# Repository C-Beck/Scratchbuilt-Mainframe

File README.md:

# Scratchbuilt-Mainframe
Mainframe design based on a z80 microprocessor

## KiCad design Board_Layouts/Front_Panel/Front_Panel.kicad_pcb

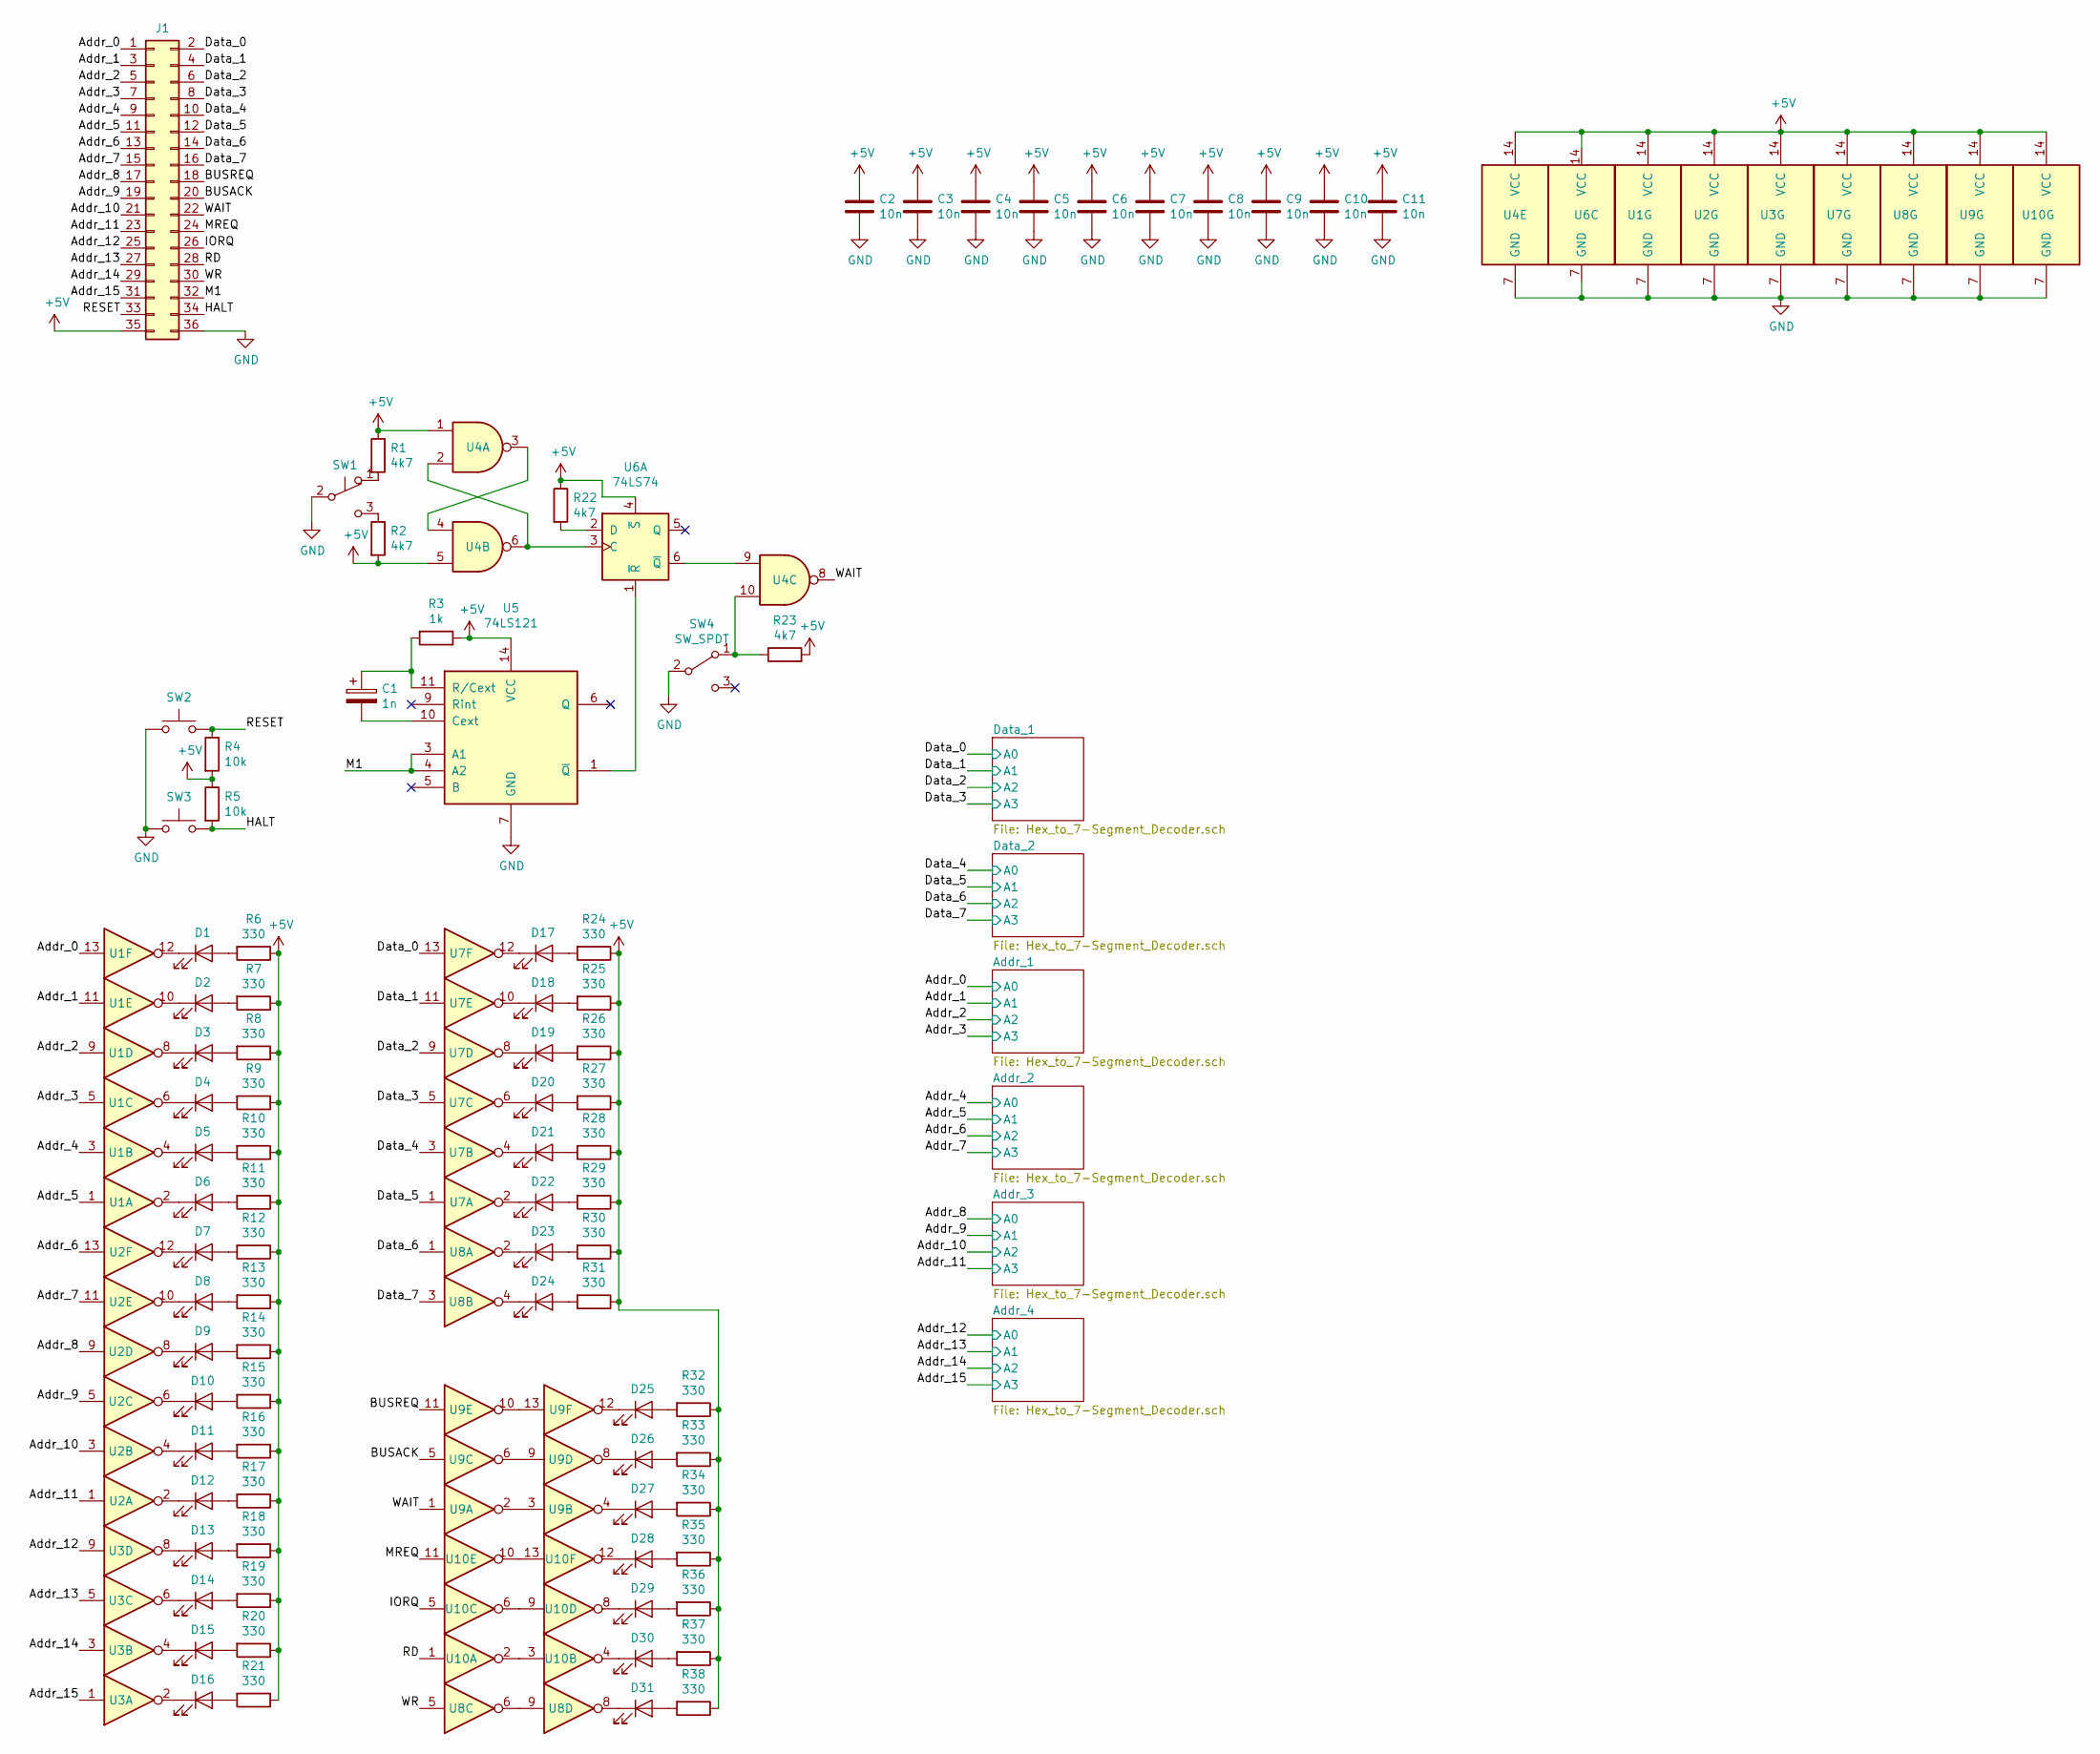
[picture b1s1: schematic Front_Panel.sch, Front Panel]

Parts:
C1: 1n; C_Rect_L4.0mm_W2.5mm_P2.50mm
C2, C3, C4, C5, C6, C7, C8, C9, C10, C11: 10n; C_Rect_L4.0mm_W2.5mm_P2.50mm
D1, D2, D3, D4, D5, D6, D7, D8, D9, D10, D11, D12, D13, D14, D15, D16, D17, D18, D19, D20, D21, D22, D23, D24, D25, D26, D27, D28, D29, D30, D31: LED; LED_D5.0mm
J1: Conn_02x18_Odd_Even; PinHeader_2x18_P2.54mm_Vertical
R1, R2, R22, R23: 4k7; R_Axial_DIN0207_L6.3mm_D2.5mm_P10.16mm_Horizontal
R3: 1k; R_Axial_DIN0207_L6.3mm_D2.5mm_P10.16mm_Horizontal
R4, R5: 10k; R_Axial_DIN0207_L6.3mm_D2.5mm_P10.16mm_Horizontal
R6, R7, R8, R9, R10, R11, R12, R13, R14, R15, R16, R17, R18, R19, R20, R21, R24, R25, R26, R27, R28, R29, R30, R31, R32, R33, R34, R35, R36, R37, R38: 330; R_Axial_DIN0207_L6.3mm_D2.5mm_P10.16mm_Horizontal
SW1: SW_Push_SPDT; PinHeader_1x03_P2.54mm_Vertical
SW2, SW3: SW_Push; PinHeader_1x03_P2.54mm_Vertical
SW4: SW_SPDT; PinHeader_1x03_P2.54mm_Vertical
U1, U2, U3, U7, U8, U9, U10: 74LS04; DIP-14_W7.62mm
U4: 7400; DIP-14_W7.62mm
U5: 74LS121; DIP-14_W7.62mm
U6: 74LS74; DIP-14_W7.62mm

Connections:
+5V: C2.1, C3.1, C4.1, C5.1, C6.1, C7.1, C8.1, C9.1, C10.1, C11.1, J1.35, R1.1, R2.2, R3.1, R4.2, R5.1, R6.1, R7.1, R8.1, R9.1, R10.1, R11.1, R12.1, R13.1, R14.1, R15.1, R16.1, R17.1, R18.1, R19.1, R20.1, R21.1, R22.1, R23.2, R24.1, R25.1, R26.1, R27.1, R28.1, R29.1, R30.1, R31.1, R32.1, R33.1, R34.1, R35.1, R36.1, R37.1, R38.1, U1.14 (VCC), U2.14 (VCC), U3.14 (VCC), U4.1, U4.5, U4.14 (VCC), U5.14 (VCC), U6.4 (~S), U6.14 (VCC), U7.14 (VCC), U8.14 (VCC), U9.14 (VCC), U10.14 (VCC); also elsewhere on the board
/Addr_0: J1.1, U1.13; also elsewhere on the board
/Addr_1: J1.3, U1.11; also elsewhere on the board
/Addr_2: J1.5, U1.9; also elsewhere on the board
/Addr_3: J1.7, U1.5; also elsewhere on the board
/Addr_4: J1.9, U1.3; also elsewhere on the board
/Addr_5: J1.11, U1.1; also elsewhere on the board
/Addr_6: J1.13, U2.13; also elsewhere on the board
/Addr_7: J1.15, U2.11; also elsewhere on the board
/Addr_8: J1.17, U2.9; also elsewhere on the board
/Addr_9: J1.19, U2.5; also elsewhere on the board
/Addr_10: J1.21, U2.3; also elsewhere on the board
/Addr_11: J1.23, U2.1; also elsewhere on the board
/Addr_12: J1.25, U3.9; also elsewhere on the board
/Addr_13: J1.27, U3.5; also elsewhere on the board
/Addr_14: J1.29, U3.3; also elsewhere on the board
/Addr_15: J1.31, U3.1; also elsewhere on the board
/BUSACK: J1.20, U9.5
/BUSREQ: J1.18, U9.11
/Data_0: J1.2, U7.13; also elsewhere on the board
/Data_1: J1.4, U7.11; also elsewhere on the board
/Data_2: J1.6, U7.9; also elsewhere on the board
/Data_3: J1.8, U7.5; also elsewhere on the board
/Data_4: J1.10, U7.3; also elsewhere on the board
/Data_5: J1.12, U7.1; also elsewhere on the board
/Data_6: J1.14, U8.1; also elsewhere on the board
/Data_7: J1.16, U8.3; also elsewhere on the board
/HALT: J1.34, R5.2, SW3.2
/IORQ: J1.26, U10.5
/M1: J1.32, U5.3 (A1), U5.4 (A2)
/MREQ: J1.24, U10.11
/RD: J1.28, U10.1
/RESET: J1.33, R4.1, SW2.2
/WAIT: J1.22, U4.8, U9.1
/WR: J1.30, U8.5
GND: C2.2, C3.2, C4.2, C5.2, C6.2, C7.2, C8.2, C9.2, C10.2, C11.2, J1.36, SW1.2 (B), SW2.1, SW3.1, SW4.2 (B), U1.7 (GND), U2.7 (GND), U3.7 (GND), U4.7 (GND), U5.7 (GND), U6.7 (GND), U7.7 (GND), U8.7 (GND), U9.7 (GND), U10.7 (GND); also elsewhere on the board
unnamed: C1.1, R3.2, U5.11 (R/Cext)
unnamed: C1.2, U5.10 (Cext)
unnamed: D1.1 (K), U1.12
unnamed: D1.2 (A), R6.2
unnamed: D2.1 (K), U1.10
unnamed: D2.2 (A), R7.2
unnamed: D3.1 (K), U1.8
unnamed: D3.2 (A), R8.2
unnamed: D4.1 (K), U1.6
unnamed: D4.2 (A), R9.2
unnamed: D5.1 (K), U1.4
unnamed: D5.2 (A), R10.2
unnamed: D6.1 (K), U1.2
unnamed: D6.2 (A), R11.2
unnamed: D7.1 (K), U2.12
unnamed: D7.2 (A), R12.2
unnamed: D8.1 (K), U2.10
unnamed: D8.2 (A), R13.2
unnamed: D9.1 (K), U2.8
unnamed: D9.2 (A), R14.2
unnamed: D10.1 (K), U2.6
unnamed: D10.2 (A), R15.2
unnamed: D11.1 (K), U2.4
unnamed: D11.2 (A), R16.2
unnamed: D12.1 (K), U2.2
unnamed: D12.2 (A), R17.2
unnamed: D13.1 (K), U3.8
unnamed: D13.2 (A), R18.2
unnamed: D14.1 (K), U3.6
unnamed: D14.2 (A), R19.2
unnamed: D15.1 (K), U3.4
unnamed: D15.2 (A), R20.2
unnamed: D16.1 (K), U3.2
unnamed: D16.2 (A), R21.2
unnamed: D17.1 (K), U7.12
unnamed: D17.2 (A), R24.2
unnamed: D18.1 (K), U7.10
unnamed: D18.2 (A), R25.2
unnamed: D19.1 (K), U7.8
unnamed: D19.2 (A), R26.2
unnamed: D20.1 (K), U7.6
unnamed: D20.2 (A), R27.2
unnamed: D21.1 (K), U7.4
unnamed: D21.2 (A), R28.2
unnamed: D22.1 (K), U7.2
unnamed: D22.2 (A), R29.2
unnamed: D23.1 (K), U8.2
unnamed: D23.2 (A), R30.2
unnamed: D24.1 (K), U8.4
unnamed: D24.2 (A), R31.2
unnamed: D25.1 (K), U9.12
unnamed: D25.2 (A), R32.2
unnamed: D26.1 (K), U9.8
unnamed: D26.2 (A), R33.2
unnamed: D27.1 (K), U9.4
unnamed: D27.2 (A), R34.2
unnamed: D28.1 (K), U10.12
unnamed: D28.2 (A), R35.2
unnamed: D29.1 (K), U10.8
unnamed: D29.2 (A), R36.2
unnamed: D30.1 (K), U10.4
unnamed: D30.2 (A), R37.2
unnamed: D31.1 (K), U8.8
unnamed: D31.2 (A), R38.2
unnamed: R1.2, SW1.1 (A)
unnamed: R2.1, SW1.3 (C)
unnamed: R22.2, U6.2 (D)
unnamed: R23.1, SW4.1 (A), U4.10
unnamed: U4.2, U4.6, U6.3 (C)
unnamed: U4.3, U4.4
unnamed: U4.9, U6.6 (~Q)
unnamed: U5.1 (~Q), U6.1 (~R)
unnamed: U8.6, U8.9
unnamed: U9.2, U9.3
unnamed: U9.6, U9.9
unnamed: U9.10, U9.13
unnamed: U10.2, U10.3
unnamed: U10.6, U10.9
unnamed: U10.10, U10.13

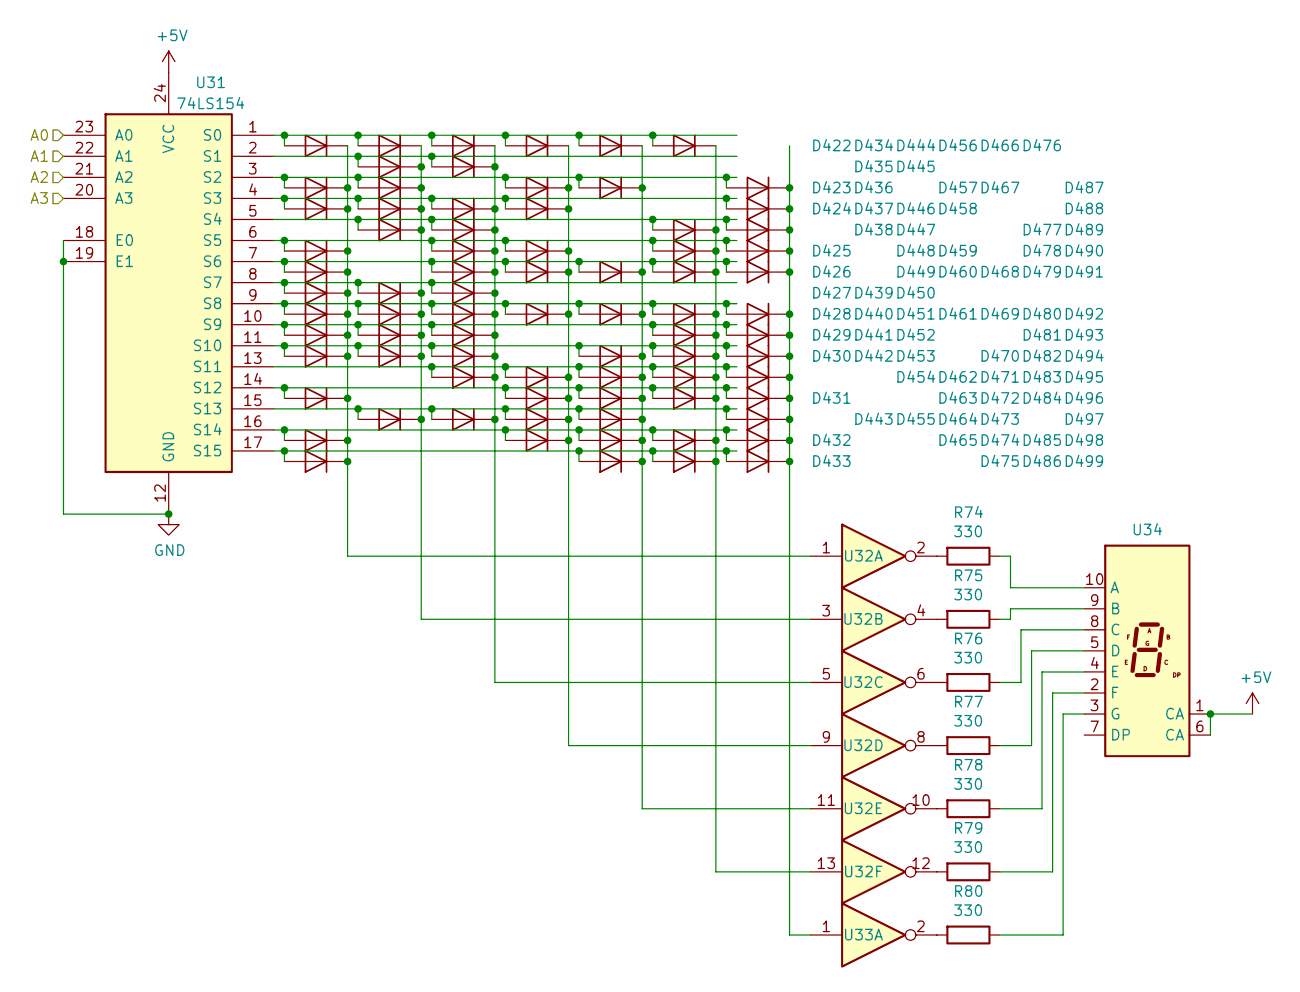
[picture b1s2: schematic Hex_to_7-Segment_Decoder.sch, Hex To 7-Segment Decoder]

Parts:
D32, D33, D34, D35, D36, D37, D38, D39, D40, D41, D42, D43, D44, D45, D46, D47, D48, D49, D50, D51, D52, D53, D54, D55, D56, D57, D58, D59, D60, D61, D62, D63, D64, D65, D66, D67, D68, D69, D70, D71, D72, D73, D74, D75, D76, D77, D78, D79, D80, D81, D82, D83, D84, D85, D86, D87, D88, D89, D90, D91, D92, D93, D94, D95, D96, D97, D98, D99, D100, D101, D102, D103, D104, D105, D106, D107, D108, D109: D; D_SOD-123
R39, R40, R41, R42, R43, R44, R45: 330; R_Axial_DIN0207_L6.3mm_D2.5mm_P10.16mm_Horizontal
U11: 74LS154; DIP-24_W7.62mm
U12, U13: 74LS04; DIP-14_W7.62mm
U14: HDSP-A401

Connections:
+5V: U11.24 (VCC), U14.1 (CA), U14.6 (CA); also elsewhere on the board
/Data_4: U11.23 (A0); also elsewhere on the board
/Data_5: U11.22 (A1); also elsewhere on the board
/Data_6: U11.21 (A2); also elsewhere on the board
/Data_7: U11.20 (A3); also elsewhere on the board
GND: U11.12 (GND), U11.18 (E0), U11.19 (E1); also elsewhere on the board
unnamed: D32.1 (K), D33.1 (K), D34.1 (K), D35.1 (K), D36.1 (K), D37.1 (K), D38.1 (K), D39.1 (K), D40.1 (K), D41.1 (K), D42.1 (K), D43.1 (K), U12.1
unnamed: D32.2 (A), D44.2 (A), D54.2 (A), D66.2 (A), D76.2 (A), D86.2 (A), U11.1 (S0)
unnamed: D33.2 (A), D46.2 (A), D67.2 (A), D77.2 (A), D97.2 (A), U11.3 (S2)
unnamed: D34.2 (A), D47.2 (A), D56.2 (A), D68.2 (A), D98.2 (A), U11.4 (S3)
unnamed: D37.2 (A), D49.2 (A), D60.2 (A), U11.8 (S7)
unnamed: D44.1 (K), D45.1 (K), D46.1 (K), D47.1 (K), D48.1 (K), D49.1 (K), D50.1 (K), D51.1 (K), D52.1 (K), D53.1 (K), U12.3
unnamed: D45.2 (A), D55.2 (A), U11.2 (S1)
unnamed: D48.2 (A), D57.2 (A), D87.2 (A), D99.2 (A), U11.5 (S4)
unnamed: D54.1 (K), D55.1 (K), D56.1 (K), D57.1 (K), D58.1 (K), D59.1 (K), D60.1 (K), D61.1 (K), D62.1 (K), D63.1 (K), D64.1 (K), D65.1 (K), U12.5
unnamed: D66.1 (K), D67.1 (K), D68.1 (K), D69.1 (K), D70.1 (K), D71.1 (K), D72.1 (K), D73.1 (K), D74.1 (K), D75.1 (K), U12.9
unnamed: D76.1 (K), D77.1 (K), D78.1 (K), D79.1 (K), D80.1 (K), D81.1 (K), D82.1 (K), D83.1 (K), D84.1 (K), D85.1 (K), U12.11
unnamed: D86.1 (K), D87.1 (K), D88.1 (K), D89.1 (K), D90.1 (K), D91.1 (K), D92.1 (K), D93.1 (K), D94.1 (K), D95.1 (K), D96.1 (K), U12.13
unnamed: D97.1 (K), D98.1 (K), D99.1 (K), D100.1 (K), D101.1 (K), D102.1 (K), D103.1 (K), D104.1 (K), D105.1 (K), D106.1 (K), D107.1 (K), D108.1 (K), D109.1 (K), U13.1
unnamed: D35.2 (A), D58.2 (A), D69.2 (A), D88.2 (A), D100.2 (A), U11.6 (S5)
unnamed: D36.2 (A), D59.2 (A), D70.2 (A), D78.2 (A), D89.2 (A), D101.2 (A), U11.7 (S6)
unnamed: D38.2 (A), D50.2 (A), D61.2 (A), D71.2 (A), D79.2 (A), D90.2 (A), D102.2 (A), U11.9 (S8)
unnamed: D39.2 (A), D51.2 (A), D62.2 (A), D91.2 (A), D103.2 (A), U11.10 (S9)
unnamed: D40.2 (A), D52.2 (A), D63.2 (A), D80.2 (A), D92.2 (A), D104.2 (A), U11.11 (S10)
unnamed: D64.2 (A), D72.2 (A), D81.2 (A), D93.2 (A), D105.2 (A), U11.13 (S11)
unnamed: D41.2 (A), D73.2 (A), D82.2 (A), D94.2 (A), D106.2 (A), U11.14 (S12)
unnamed: D53.2 (A), D65.2 (A), D74.2 (A), D83.2 (A), D107.2 (A), U11.15 (S13)
unnamed: D42.2 (A), D75.2 (A), D84.2 (A), D95.2 (A), D108.2 (A), U11.16 (S14)
unnamed: D43.2 (A), D85.2 (A), D96.2 (A), D109.2 (A), U11.17 (S15)
unnamed: R39.1, U14.10 (A)
unnamed: R39.2, U12.2
unnamed: R40.1, U14.9 (B)
unnamed: R40.2, U12.4
unnamed: R41.1, U14.8 (C)
unnamed: R41.2, U12.6
unnamed: R42.1, U14.5 (D)
unnamed: R42.2, U12.8
unnamed: R43.1, U14.4 (E)
unnamed: R43.2, U12.10
unnamed: R44.1, U14.2 (F)
unnamed: R44.2, U12.12
unnamed: R45.1, U14.3 (G)
unnamed: R45.2, U13.2

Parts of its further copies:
D110, D111, D112, D113, D114, D115, D116, D117, D118, D119, D120, D121, D122, D123, D124, D125, D126, D127, D128, D129, D130, D131, D132, D133, D134, D135, D136, D137, D138, D139, D140, D141, D142, D143, D144, D145, D146, D147, D148, D149, D150, D151, D152, D153, D154, D155, D156, D157, D158, D159, D160, D161, D162, D163, D164, D165, D166, D167, D168, D169, D170, D171, D172, D173, D174, D175, D176, D177, D178, D179, D180, D181, D182, D183, D184, D185, D186, D187, D188, D189, D190, D191, D192, D193, D194, D195, D196, D197, D198, D199, D200, D201, D202, D203, D204, D205, D206, D207, D208, D209, D210, D211, D212, D213, D214, D215, D216, D217, D218, D219, D220, D221, D222, D223, D224, D225, D226, D227, D228, D229, D230, D231, D232, D233, D234, D235, D236, D237, D238, D239, D240, D241, D242, D243, D244, D245, D246, D247, D248, D249, D250, D251, D252, D253, D254, D255, D256, D257, D258, D259, D260, D261, D262, D263, D264, D265, D266, D267, D268, D269, D270, D271, D272, D273, D274, D275, D276, D277, D278, D279, D280, D281, D282, D283, D284, D285, D286, D287, D288, D289, D290, D291, D292, D293, D294, D295, D296, D297, D298, D299, D300, D301, D302, D303, D304, D305, D306, D307, D308, D309, D310, D311, D312, D313, D314, D315, D316, D317, D318, D319, D320, D321, D322, D323, D324, D325, D326, D327, D328, D329, D330, D331, D332, D333, D334, D335, D336, D337, D338, D339, D340, D341, D342, D343, D344, D345, D346, D347, D348, D349, D350, D351, D352, D353, D354, D355, D356, D357, D358, D359, D360, D361, D362, D363, D364, D365, D366, D367, D368, D369, D370, D371, D372, D373, D374, D375, D376, D377, D378, D379, D380, D381, D382, D383, D384, D385, D386, D387, D388, D389, D390, D391, D392, D393, D394, D395, D396, D397, D398, D399, D400, D401, D402, D403, D404, D405, D406, D407, D408, D409, D410, D411, D412, D413, D414, D415, D416, D417, D418, D419, D420, D421, D422, D423, D424, D425, D426, D427, D428, D429, D430, D431, D432, D433, D434, D435, D436, D437, D438, D439, D440, D441, D442, D443, D444, D445, D446, D447, D448, D449, D450, D451, D452, D453, D454, D455, D456, D457, D458, D459, D460, D461, D462, D463, D464, D465, D466, D467, D468, D469, D470, D471, D472, D473, D474, D475, D476, D477, D478, D479, D480, D481, D482, D483, D484, D485, D486, D487, D488, D489, D490, D491, D492, D493, D494, D495, D496, D497, D498, D499: D; D_SOD-123
R46, R47, R48, R49, R50, R51, R52, R53, R54, R55, R56, R57, R58, R59, R60, R61, R62, R63, R64, R65, R66, R67, R68, R69, R70, R71, R72, R73, R74, R75, R76, R77, R78, R79, R80: 330; R_Axial_DIN0207_L6.3mm_D2.5mm_P10.16mm_Horizontal
U15, U19, U23, U27, U31: 74LS154; DIP-24_W7.62mm
U16, U17, U20, U21, U24, U25, U28, U29, U32, U33: 74LS04; DIP-14_W7.62mm
U18, U22, U26, U30, U34: HDSP-A401

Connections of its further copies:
+5V: U15.24 (VCC), U18.1 (CA), U18.6 (CA), U19.24 (VCC), U22.1 (CA), U22.6 (CA), U23.24 (VCC), U26.1 (CA), U26.6 (CA), U27.24 (VCC), U30.1 (CA), U30.6 (CA), U31.24 (VCC), U34.1 (CA), U34.6 (CA); also elsewhere on the board
/Addr_0: U31.23 (A0); also elsewhere on the board
/Addr_1: U31.22 (A1); also elsewhere on the board
/Addr_2: U31.21 (A2); also elsewhere on the board
/Addr_3: U31.20 (A3); also elsewhere on the board
/Addr_4: U27.23 (A0); also elsewhere on the board
/Addr_5: U27.22 (A1); also elsewhere on the board
/Addr_6: U27.21 (A2); also elsewhere on the board
/Addr_7: U27.20 (A3); also elsewhere on the board
/Addr_8: U23.23 (A0); also elsewhere on the board
/Addr_9: U23.22 (A1); also elsewhere on the board
/Addr_10: U23.21 (A2); also elsewhere on the board
/Addr_11: U23.20 (A3); also elsewhere on the board
/Addr_12: U19.23 (A0); also elsewhere on the board
/Addr_13: U19.22 (A1); also elsewhere on the board
/Addr_14: U19.21 (A2); also elsewhere on the board
/Addr_15: U19.20 (A3); also elsewhere on the board
/Data_0: U15.23 (A0); also elsewhere on the board
/Data_1: U15.22 (A1); also elsewhere on the board
/Data_2: U15.21 (A2); also elsewhere on the board
/Data_3: U15.20 (A3); also elsewhere on the board
GND: U15.12 (GND), U15.18 (E0), U15.19 (E1), U19.12 (GND), U19.18 (E0), U19.19 (E1), U23.12 (GND), U23.18 (E0), U23.19 (E1), U27.12 (GND), U27.18 (E0), U27.19 (E1), U31.12 (GND), U31.18 (E0), U31.19 (E1); also elsewhere on the board
unnamed: D110.1 (K), D111.1 (K), D112.1 (K), D113.1 (K), D114.1 (K), D115.1 (K), D116.1 (K), D117.1 (K), D118.1 (K), D119.1 (K), D120.1 (K), D121.1 (K), U16.1
unnamed: D110.2 (A), D122.2 (A), D132.2 (A), D144.2 (A), D154.2 (A), D164.2 (A), U15.1 (S0)
unnamed: D111.2 (A), D124.2 (A), D145.2 (A), D155.2 (A), D175.2 (A), U15.3 (S2)
unnamed: D112.2 (A), D125.2 (A), D134.2 (A), D146.2 (A), D176.2 (A), U15.4 (S3)
unnamed: D113.2 (A), D136.2 (A), D147.2 (A), D166.2 (A), D178.2 (A), U15.6 (S5)
unnamed: D114.2 (A), D137.2 (A), D148.2 (A), D156.2 (A), D167.2 (A), D179.2 (A), U15.7 (S6)
unnamed: D115.2 (A), D127.2 (A), D138.2 (A), U15.8 (S7)
unnamed: D116.2 (A), D128.2 (A), D139.2 (A), D149.2 (A), D157.2 (A), D168.2 (A), D180.2 (A), U15.9 (S8)
unnamed: D117.2 (A), D129.2 (A), D140.2 (A), D169.2 (A), D181.2 (A), U15.10 (S9)
unnamed: D118.2 (A), D130.2 (A), D141.2 (A), D158.2 (A), D170.2 (A), D182.2 (A), U15.11 (S10)
unnamed: D119.2 (A), D151.2 (A), D160.2 (A), D172.2 (A), D184.2 (A), U15.14 (S12)
unnamed: D120.2 (A), D153.2 (A), D162.2 (A), D173.2 (A), D186.2 (A), U15.16 (S14)
unnamed: D121.2 (A), D163.2 (A), D174.2 (A), D187.2 (A), U15.17 (S15)
unnamed: D122.1 (K), D123.1 (K), D124.1 (K), D125.1 (K), D126.1 (K), D127.1 (K), D128.1 (K), D129.1 (K), D130.1 (K), D131.1 (K), U16.3
unnamed: D123.2 (A), D133.2 (A), U15.2 (S1)
unnamed: D126.2 (A), D135.2 (A), D165.2 (A), D177.2 (A), U15.5 (S4)
unnamed: D131.2 (A), D143.2 (A), D152.2 (A), D161.2 (A), D185.2 (A), U15.15 (S13)
unnamed: D132.1 (K), D133.1 (K), D134.1 (K), D135.1 (K), D136.1 (K), D137.1 (K), D138.1 (K), D139.1 (K), D140.1 (K), D141.1 (K), D142.1 (K), D143.1 (K), U16.5
unnamed: D142.2 (A), D150.2 (A), D159.2 (A), D171.2 (A), D183.2 (A), U15.13 (S11)
unnamed: D144.1 (K), D145.1 (K), D146.1 (K), D147.1 (K), D148.1 (K), D149.1 (K), D150.1 (K), D151.1 (K), D152.1 (K), D153.1 (K), U16.9
unnamed: D154.1 (K), D155.1 (K), D156.1 (K), D157.1 (K), D158.1 (K), D159.1 (K), D160.1 (K), D161.1 (K), D162.1 (K), D163.1 (K), U16.11
unnamed: D164.1 (K), D165.1 (K), D166.1 (K), D167.1 (K), D168.1 (K), D169.1 (K), D170.1 (K), D171.1 (K), D172.1 (K), D173.1 (K), D174.1 (K), U16.13
unnamed: D175.1 (K), D176.1 (K), D177.1 (K), D178.1 (K), D179.1 (K), D180.1 (K), D181.1 (K), D182.1 (K), D183.1 (K), D184.1 (K), D185.1 (K), D186.1 (K), D187.1 (K), U17.1
unnamed: D188.1 (K), D189.1 (K), D190.1 (K), D191.1 (K), D192.1 (K), D193.1 (K), D194.1 (K), D195.1 (K), D196.1 (K), D197.1 (K), D198.1 (K), D199.1 (K), U20.1
unnamed: D188.2 (A), D200.2 (A), D210.2 (A), D222.2 (A), D232.2 (A), D242.2 (A), U19.1 (S0)
unnamed: D189.2 (A), D202.2 (A), D223.2 (A), D233.2 (A), D253.2 (A), U19.3 (S2)
unnamed: D190.2 (A), D203.2 (A), D212.2 (A), D224.2 (A), D254.2 (A), U19.4 (S3)
unnamed: D191.2 (A), D214.2 (A), D225.2 (A), D244.2 (A), D256.2 (A), U19.6 (S5)
unnamed: D192.2 (A), D215.2 (A), D226.2 (A), D234.2 (A), D245.2 (A), D257.2 (A), U19.7 (S6)
unnamed: D193.2 (A), D205.2 (A), D216.2 (A), U19.8 (S7)
unnamed: D194.2 (A), D206.2 (A), D217.2 (A), D227.2 (A), D235.2 (A), D246.2 (A), D258.2 (A), U19.9 (S8)
unnamed: D195.2 (A), D207.2 (A), D218.2 (A), D247.2 (A), D259.2 (A), U19.10 (S9)
unnamed: D196.2 (A), D208.2 (A), D219.2 (A), D236.2 (A), D248.2 (A), D260.2 (A), U19.11 (S10)
unnamed: D197.2 (A), D229.2 (A), D238.2 (A), D250.2 (A), D262.2 (A), U19.14 (S12)
unnamed: D198.2 (A), D231.2 (A), D240.2 (A), D251.2 (A), D264.2 (A), U19.16 (S14)
unnamed: D199.2 (A), D241.2 (A), D252.2 (A), D265.2 (A), U19.17 (S15)
unnamed: D200.1 (K), D201.1 (K), D202.1 (K), D203.1 (K), D204.1 (K), D205.1 (K), D206.1 (K), D207.1 (K), D208.1 (K), D209.1 (K), U20.3
unnamed: D201.2 (A), D211.2 (A), U19.2 (S1)
unnamed: D204.2 (A), D213.2 (A), D243.2 (A), D255.2 (A), U19.5 (S4)
unnamed: D209.2 (A), D221.2 (A), D230.2 (A), D239.2 (A), D263.2 (A), U19.15 (S13)
unnamed: D210.1 (K), D211.1 (K), D212.1 (K), D213.1 (K), D214.1 (K), D215.1 (K), D216.1 (K), D217.1 (K), D218.1 (K), D219.1 (K), D220.1 (K), D221.1 (K), U20.5
unnamed: D220.2 (A), D228.2 (A), D237.2 (A), D249.2 (A), D261.2 (A), U19.13 (S11)
unnamed: D222.1 (K), D223.1 (K), D224.1 (K), D225.1 (K), D226.1 (K), D227.1 (K), D228.1 (K), D229.1 (K), D230.1 (K), D231.1 (K), U20.9
unnamed: D232.1 (K), D233.1 (K), D234.1 (K), D235.1 (K), D236.1 (K), D237.1 (K), D238.1 (K), D239.1 (K), D240.1 (K), D241.1 (K), U20.11
unnamed: D242.1 (K), D243.1 (K), D244.1 (K), D245.1 (K), D246.1 (K), D247.1 (K), D248.1 (K), D249.1 (K), D250.1 (K), D251.1 (K), D252.1 (K), U20.13
unnamed: D253.1 (K), D254.1 (K), D255.1 (K), D256.1 (K), D257.1 (K), D258.1 (K), D259.1 (K), D260.1 (K), D261.1 (K), D262.1 (K), D263.1 (K), D264.1 (K), D265.1 (K), U21.1
unnamed: D266.1 (K), D267.1 (K), D268.1 (K), D269.1 (K), D270.1 (K), D271.1 (K), D272.1 (K), D273.1 (K), D274.1 (K), D275.1 (K), D276.1 (K), D277.1 (K), U24.1
unnamed: D266.2 (A), D278.2 (A), D288.2 (A), D300.2 (A), D310.2 (A), D320.2 (A), U23.1 (S0)
unnamed: D267.2 (A), D280.2 (A), D301.2 (A), D311.2 (A), D331.2 (A), U23.3 (S2)
unnamed: D268.2 (A), D281.2 (A), D290.2 (A), D302.2 (A), D332.2 (A), U23.4 (S3)
unnamed: D269.2 (A), D292.2 (A), D303.2 (A), D322.2 (A), D334.2 (A), U23.6 (S5)
unnamed: D270.2 (A), D293.2 (A), D304.2 (A), D312.2 (A), D323.2 (A), D335.2 (A), U23.7 (S6)
unnamed: D271.2 (A), D283.2 (A), D294.2 (A), U23.8 (S7)
unnamed: D272.2 (A), D284.2 (A), D295.2 (A), D305.2 (A), D313.2 (A), D324.2 (A), D336.2 (A), U23.9 (S8)
unnamed: D273.2 (A), D285.2 (A), D296.2 (A), D325.2 (A), D337.2 (A), U23.10 (S9)
unnamed: D274.2 (A), D286.2 (A), D297.2 (A), D314.2 (A), D326.2 (A), D338.2 (A), U23.11 (S10)
unnamed: D275.2 (A), D307.2 (A), D316.2 (A), D328.2 (A), D340.2 (A), U23.14 (S12)
unnamed: D276.2 (A), D309.2 (A), D318.2 (A), D329.2 (A), D342.2 (A), U23.16 (S14)
unnamed: D277.2 (A), D319.2 (A), D330.2 (A), D343.2 (A), U23.17 (S15)
unnamed: D278.1 (K), D279.1 (K), D280.1 (K), D281.1 (K), D282.1 (K), D283.1 (K), D284.1 (K), D285.1 (K), D286.1 (K), D287.1 (K), U24.3
unnamed: D279.2 (A), D289.2 (A), U23.2 (S1)
unnamed: D282.2 (A), D291.2 (A), D321.2 (A), D333.2 (A), U23.5 (S4)
unnamed: D287.2 (A), D299.2 (A), D308.2 (A), D317.2 (A), D341.2 (A), U23.15 (S13)
unnamed: D288.1 (K), D289.1 (K), D290.1 (K), D291.1 (K), D292.1 (K), D293.1 (K), D294.1 (K), D295.1 (K), D296.1 (K), D297.1 (K), D298.1 (K), D299.1 (K), U24.5
unnamed: D298.2 (A), D306.2 (A), D315.2 (A), D327.2 (A), D339.2 (A), U23.13 (S11)
unnamed: D300.1 (K), D301.1 (K), D302.1 (K), D303.1 (K), D304.1 (K), D305.1 (K), D306.1 (K), D307.1 (K), D308.1 (K), D309.1 (K), U24.9
unnamed: D310.1 (K), D311.1 (K), D312.1 (K), D313.1 (K), D314.1 (K), D315.1 (K), D316.1 (K), D317.1 (K), D318.1 (K), D319.1 (K), U24.11
unnamed: D320.1 (K), D321.1 (K), D322.1 (K), D323.1 (K), D324.1 (K), D325.1 (K), D326.1 (K), D327.1 (K), D328.1 (K), D329.1 (K), D330.1 (K), U24.13
unnamed: D331.1 (K), D332.1 (K), D333.1 (K), D334.1 (K), D335.1 (K), D336.1 (K), D337.1 (K), D338.1 (K), D339.1 (K), D340.1 (K), D341.1 (K), D342.1 (K), D343.1 (K), U25.1
unnamed: D344.1 (K), D345.1 (K), D346.1 (K), D347.1 (K), D348.1 (K), D349.1 (K), D350.1 (K), D351.1 (K), D352.1 (K), D353.1 (K), D354.1 (K), D355.1 (K), U28.1
unnamed: D344.2 (A), D356.2 (A), D366.2 (A), D378.2 (A), D388.2 (A), D398.2 (A), U27.1 (S0)
unnamed: D345.2 (A), D358.2 (A), D379.2 (A), D389.2 (A), D409.2 (A), U27.3 (S2)
unnamed: D346.2 (A), D359.2 (A), D368.2 (A), D380.2 (A), D410.2 (A), U27.4 (S3)
unnamed: D347.2 (A), D370.2 (A), D381.2 (A), D400.2 (A), D412.2 (A), U27.6 (S5)
unnamed: D348.2 (A), D371.2 (A), D382.2 (A), D390.2 (A), D401.2 (A), D413.2 (A), U27.7 (S6)
unnamed: D349.2 (A), D361.2 (A), D372.2 (A), U27.8 (S7)
unnamed: D350.2 (A), D362.2 (A), D373.2 (A), D383.2 (A), D391.2 (A), D402.2 (A), D414.2 (A), U27.9 (S8)
unnamed: D351.2 (A), D363.2 (A), D374.2 (A), D403.2 (A), D415.2 (A), U27.10 (S9)
unnamed: D352.2 (A), D364.2 (A), D375.2 (A), D392.2 (A), D404.2 (A), D416.2 (A), U27.11 (S10)
unnamed: D353.2 (A), D385.2 (A), D394.2 (A), D406.2 (A), D418.2 (A), U27.14 (S12)
unnamed: D354.2 (A), D387.2 (A), D396.2 (A), D407.2 (A), D420.2 (A), U27.16 (S14)
unnamed: D355.2 (A), D397.2 (A), D408.2 (A), D421.2 (A), U27.17 (S15)
unnamed: D356.1 (K), D357.1 (K), D358.1 (K), D359.1 (K), D360.1 (K), D361.1 (K), D362.1 (K), D363.1 (K), D364.1 (K), D365.1 (K), U28.3
unnamed: D357.2 (A), D367.2 (A), U27.2 (S1)
unnamed: D360.2 (A), D369.2 (A), D399.2 (A), D411.2 (A), U27.5 (S4)
unnamed: D365.2 (A), D377.2 (A), D386.2 (A), D395.2 (A), D419.2 (A), U27.15 (S13)
unnamed: D366.1 (K), D367.1 (K), D368.1 (K), D369.1 (K), D370.1 (K), D371.1 (K), D372.1 (K), D373.1 (K), D374.1 (K), D375.1 (K), D376.1 (K), D377.1 (K), U28.5
unnamed: D376.2 (A), D384.2 (A), D393.2 (A), D405.2 (A), D417.2 (A), U27.13 (S11)
unnamed: D378.1 (K), D379.1 (K), D380.1 (K), D381.1 (K), D382.1 (K), D383.1 (K), D384.1 (K), D385.1 (K), D386.1 (K), D387.1 (K), U28.9
unnamed: D388.1 (K), D389.1 (K), D390.1 (K), D391.1 (K), D392.1 (K), D393.1 (K), D394.1 (K), D395.1 (K), D396.1 (K), D397.1 (K), U28.11
unnamed: D398.1 (K), D399.1 (K), D400.1 (K), D401.1 (K), D402.1 (K), D403.1 (K), D404.1 (K), D405.1 (K), D406.1 (K), D407.1 (K), D408.1 (K), U28.13
unnamed: D409.1 (K), D410.1 (K), D411.1 (K), D412.1 (K), D413.1 (K), D414.1 (K), D415.1 (K), D416.1 (K), D417.1 (K), D418.1 (K), D419.1 (K), D420.1 (K), D421.1 (K), U29.1
unnamed: D422.1 (K), D423.1 (K), D424.1 (K), D425.1 (K), D426.1 (K), D427.1 (K), D428.1 (K), D429.1 (K), D430.1 (K), D431.1 (K), D432.1 (K), D433.1 (K), U32.1
unnamed: D422.2 (A), D434.2 (A), D444.2 (A), D456.2 (A), D466.2 (A), D476.2 (A), U31.1 (S0)
unnamed: D423.2 (A), D436.2 (A), D457.2 (A), D467.2 (A), D487.2 (A), U31.3 (S2)
unnamed: D424.2 (A), D437.2 (A), D446.2 (A), D458.2 (A), D488.2 (A), U31.4 (S3)
unnamed: D425.2 (A), D448.2 (A), D459.2 (A), D478.2 (A), D490.2 (A), U31.6 (S5)
unnamed: D426.2 (A), D449.2 (A), D460.2 (A), D468.2 (A), D479.2 (A), D491.2 (A), U31.7 (S6)
unnamed: D427.2 (A), D439.2 (A), D450.2 (A), U31.8 (S7)
unnamed: D428.2 (A), D440.2 (A), D451.2 (A), D461.2 (A), D469.2 (A), D480.2 (A), D492.2 (A), U31.9 (S8)
unnamed: D429.2 (A), D441.2 (A), D452.2 (A), D481.2 (A), D493.2 (A), U31.10 (S9)
unnamed: D430.2 (A), D442.2 (A), D453.2 (A), D470.2 (A), D482.2 (A), D494.2 (A), U31.11 (S10)
unnamed: D431.2 (A), D463.2 (A), D472.2 (A), D484.2 (A), D496.2 (A), U31.14 (S12)
unnamed: D432.2 (A), D465.2 (A), D474.2 (A), D485.2 (A), D498.2 (A), U31.16 (S14)
unnamed: D433.2 (A), D475.2 (A), D486.2 (A), D499.2 (A), U31.17 (S15)
unnamed: D434.1 (K), D435.1 (K), D436.1 (K), D437.1 (K), D438.1 (K), D439.1 (K), D440.1 (K), D441.1 (K), D442.1 (K), D443.1 (K), U32.3
unnamed: D435.2 (A), D445.2 (A), U31.2 (S1)
unnamed: D438.2 (A), D447.2 (A), D477.2 (A), D489.2 (A), U31.5 (S4)
unnamed: D443.2 (A), D455.2 (A), D464.2 (A), D473.2 (A), D497.2 (A), U31.15 (S13)
unnamed: D444.1 (K), D445.1 (K), D446.1 (K), D447.1 (K), D448.1 (K), D449.1 (K), D450.1 (K), D451.1 (K), D452.1 (K), D453.1 (K), D454.1 (K), D455.1 (K), U32.5
unnamed: D454.2 (A), D462.2 (A), D471.2 (A), D483.2 (A), D495.2 (A), U31.13 (S11)
unnamed: D456.1 (K), D457.1 (K), D458.1 (K), D459.1 (K), D460.1 (K), D461.1 (K), D462.1 (K), D463.1 (K), D464.1 (K), D465.1 (K), U32.9
unnamed: D466.1 (K), D467.1 (K), D468.1 (K), D469.1 (K), D470.1 (K), D471.1 (K), D472.1 (K), D473.1 (K), D474.1 (K), D475.1 (K), U32.11
unnamed: D476.1 (K), D477.1 (K), D478.1 (K), D479.1 (K), D480.1 (K), D481.1 (K), D482.1 (K), D483.1 (K), D484.1 (K), D485.1 (K), D486.1 (K), U32.13
unnamed: D487.1 (K), D488.1 (K), D489.1 (K), D490.1 (K), D491.1 (K), D492.1 (K), D493.1 (K), D494.1 (K), D495.1 (K), D496.1 (K), D497.1 (K), D498.1 (K), D499.1 (K), U33.1
unnamed: R46.1, U18.10 (A)
unnamed: R46.2, U16.2
unnamed: R47.1, U18.9 (B)
unnamed: R47.2, U16.4
unnamed: R48.1, U18.8 (C)
unnamed: R48.2, U16.6
unnamed: R49.1, U18.5 (D)
unnamed: R49.2, U16.8
unnamed: R50.1, U18.4 (E)
unnamed: R50.2, U16.10
unnamed: R51.1, U18.2 (F)
unnamed: R51.2, U16.12
unnamed: R52.1, U18.3 (G)
unnamed: R52.2, U17.2
unnamed: R53.1, U22.10 (A)
unnamed: R53.2, U20.2
unnamed: R54.1, U22.9 (B)
unnamed: R54.2, U20.4
unnamed: R55.1, U22.8 (C)
unnamed: R55.2, U20.6
unnamed: R56.1, U22.5 (D)
unnamed: R56.2, U20.8
unnamed: R57.1, U22.4 (E)
unnamed: R57.2, U20.10
unnamed: R58.1, U22.2 (F)
unnamed: R58.2, U20.12
unnamed: R59.1, U22.3 (G)
unnamed: R59.2, U21.2
unnamed: R60.1, U26.10 (A)
unnamed: R60.2, U24.2
unnamed: R61.1, U26.9 (B)
unnamed: R61.2, U24.4
unnamed: R62.1, U26.8 (C)
unnamed: R62.2, U24.6
unnamed: R63.1, U26.5 (D)
unnamed: R63.2, U24.8
unnamed: R64.1, U26.4 (E)
unnamed: R64.2, U24.10
unnamed: R65.1, U26.2 (F)
unnamed: R65.2, U24.12
unnamed: R66.1, U26.3 (G)
unnamed: R66.2, U25.2
unnamed: R67.1, U30.10 (A)
unnamed: R67.2, U28.2
unnamed: R68.1, U30.9 (B)
unnamed: R68.2, U28.4
unnamed: R69.1, U30.8 (C)
unnamed: R69.2, U28.6
unnamed: R70.1, U30.5 (D)
unnamed: R70.2, U28.8
unnamed: R71.1, U30.4 (E)
unnamed: R71.2, U28.10
unnamed: R72.1, U30.2 (F)
unnamed: R72.2, U28.12
unnamed: R73.1, U30.3 (G)
unnamed: R73.2, U29.2
unnamed: R74.1, U34.10 (A)
unnamed: R74.2, U32.2
unnamed: R75.1, U34.9 (B)
unnamed: R75.2, U32.4
unnamed: R76.1, U34.8 (C)
unnamed: R76.2, U32.6
unnamed: R77.1, U34.5 (D)
unnamed: R77.2, U32.8
unnamed: R78.1, U34.4 (E)
unnamed: R78.2, U32.10
unnamed: R79.1, U34.2 (F)
unnamed: R79.2, U32.12
unnamed: R80.1, U34.3 (G)
unnamed: R80.2, U33.2

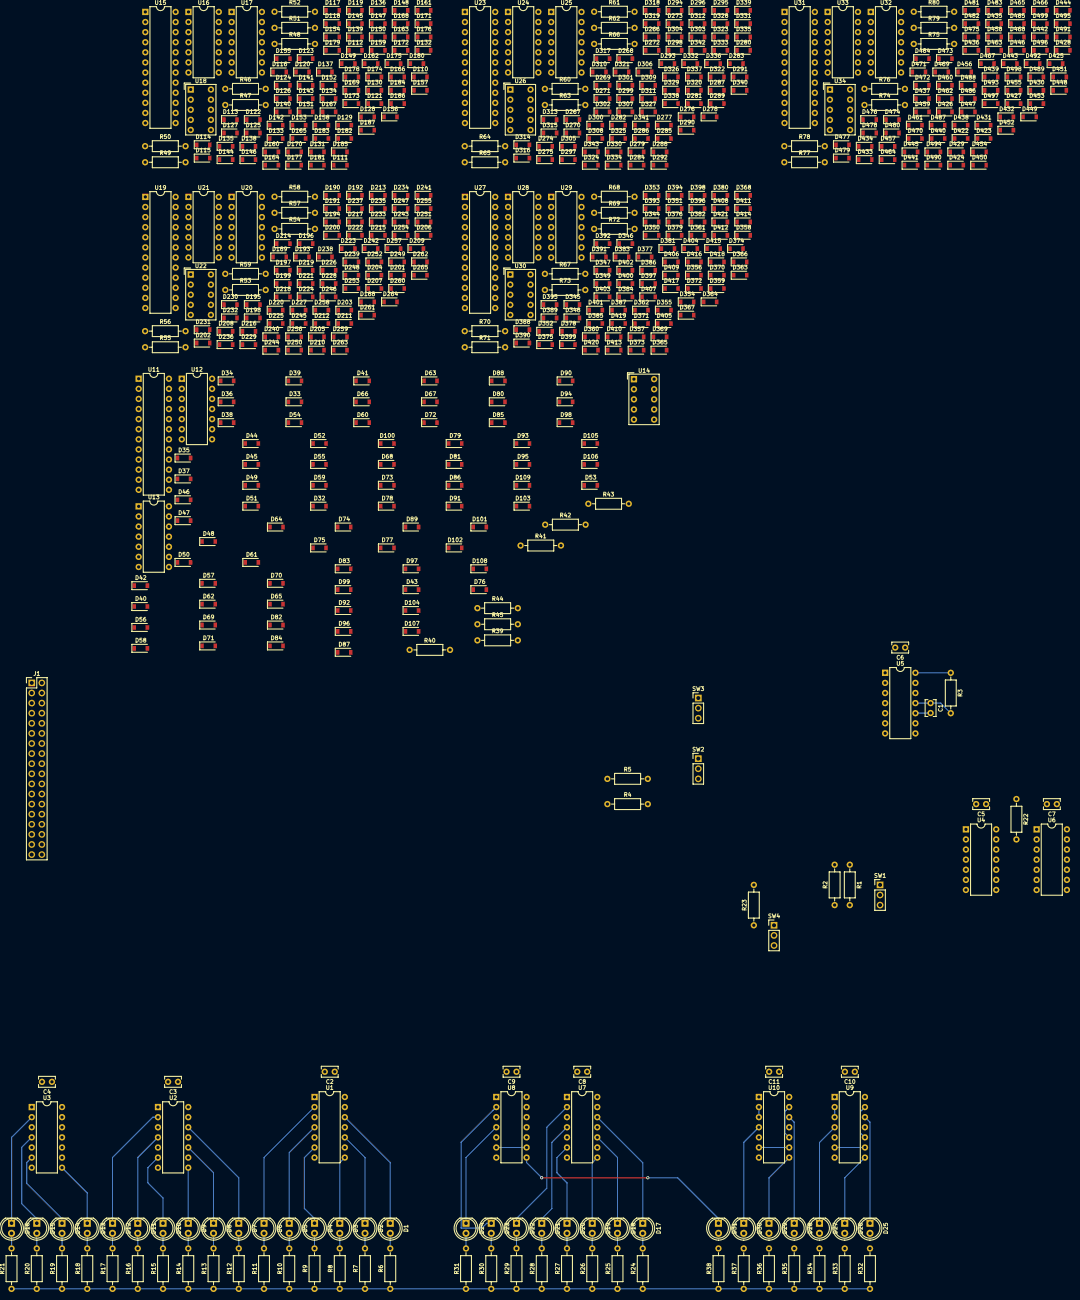
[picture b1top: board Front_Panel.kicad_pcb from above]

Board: 2 copper layers, 629 parts (0 on the bottom side), 337 nets.
